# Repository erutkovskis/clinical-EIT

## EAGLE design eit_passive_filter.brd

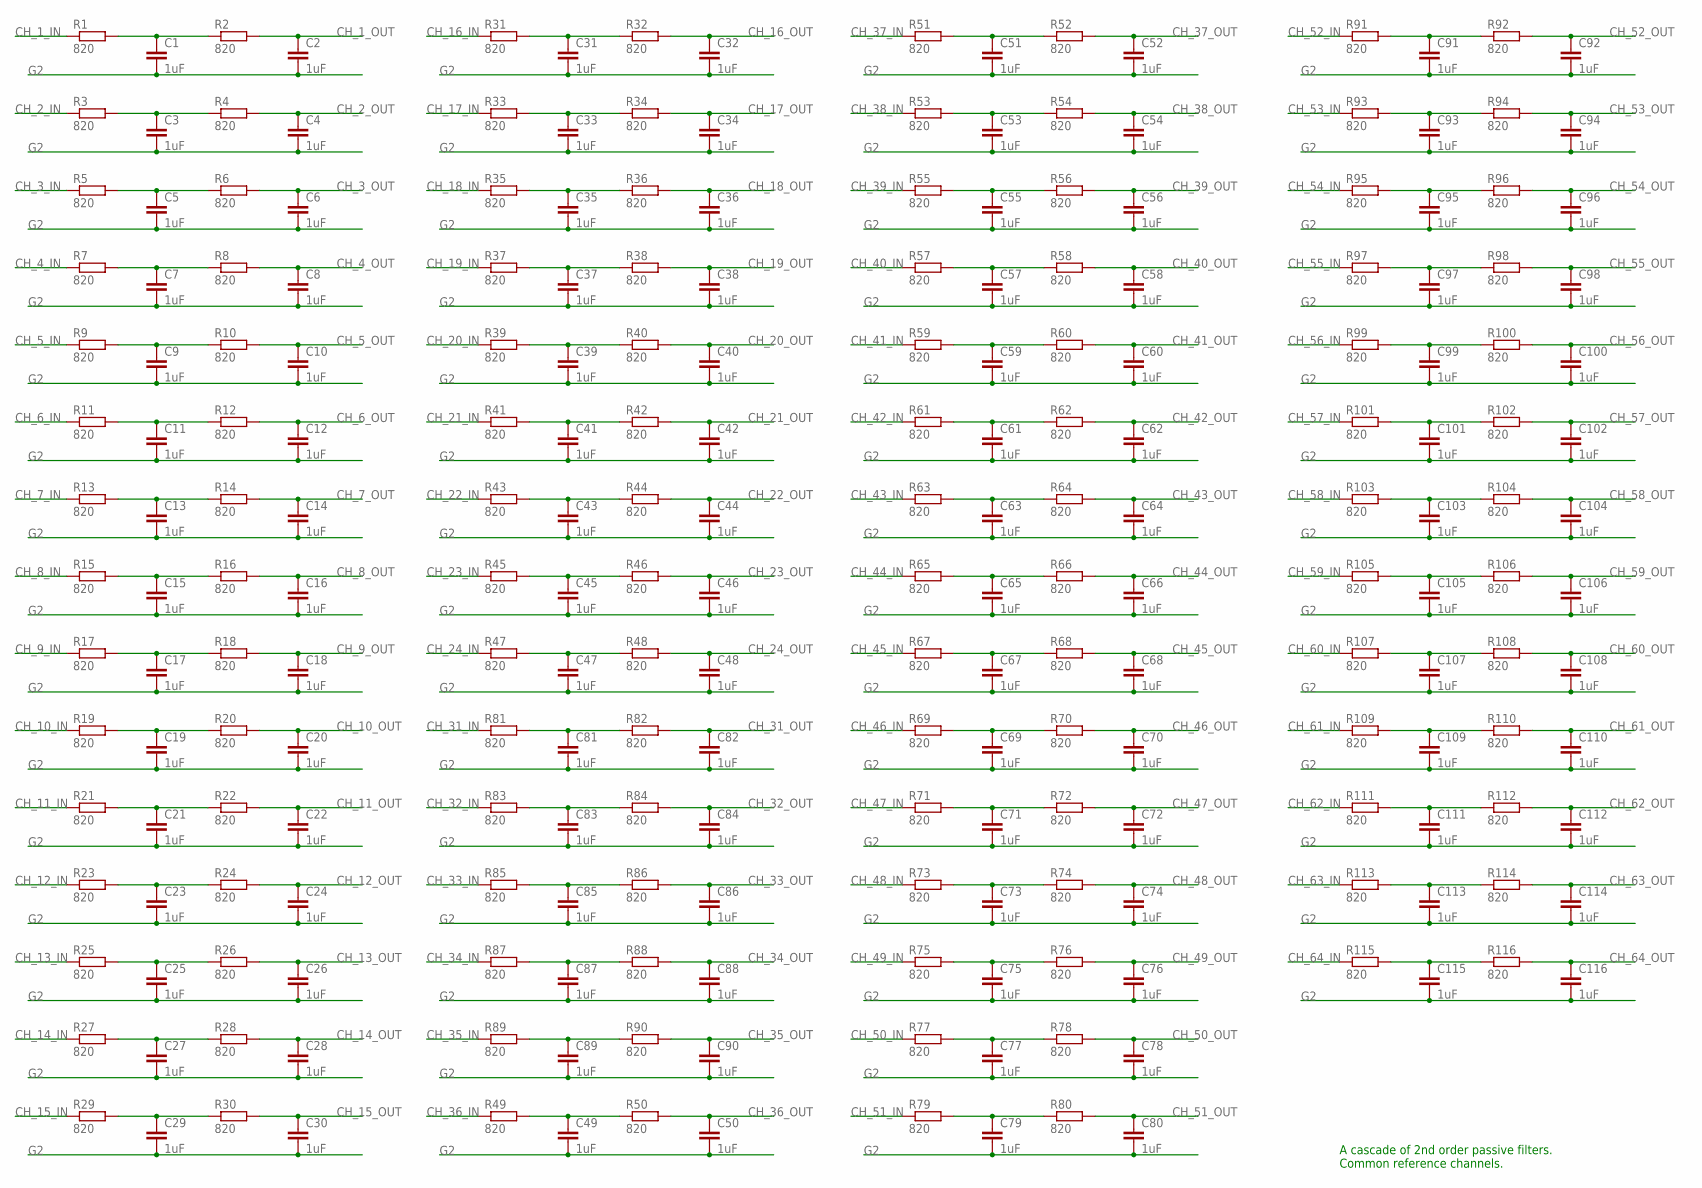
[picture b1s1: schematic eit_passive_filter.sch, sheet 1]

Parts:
C1, C2, C3, C4, C5, C6, C7, C8, C9, C10, C11, C12, C13, C14, C15, C16, C17, C18, C19, C20, C21, C22, C23, C24, C25, C26, C27, C28, C29, C30, C31, C32, C33, C34, C35, C36, C37, C38, C39, C40, C41, C42, C43, C44, C45, C46, C47, C48, C49, C50, C51, C52, C53, C54, C55, C56, C57, C58, C59, C60, C61, C62, C63, C64, C65, C66, C67, C68, C69, C70, C71, C72, C73, C74, C75, C76, C77, C78, C79, C80, C81, C82, C83, C84, C85, C86, C87, C88, C89, C90, C91, C92, C93, C94, C95, C96, C97, C98, C99, C100, C101, C102, C103, C104, C105, C106, C107, C108, C109, C110, C111, C112, C113, C114, C115, C116: 1uF; C0402
R1, R2, R3, R4, R5, R6, R7, R8, R9, R10, R11, R12, R13, R14, R15, R16, R17, R18, R19, R20, R21, R22, R23, R24, R25, R26, R27, R28, R29, R30, R31, R32, R33, R34, R35, R36, R37, R38, R39, R40, R41, R42, R43, R44, R45, R46, R47, R48, R49, R50, R51, R52, R53, R54, R55, R56, R57, R58, R59, R60, R61, R62, R63, R64, R65, R66, R67, R68, R69, R70, R71, R72, R73, R74, R75, R76, R77, R78, R79, R80, R81, R82, R83, R84, R85, R86, R87, R88, R89, R90, R91, R92, R93, R94, R95, R96, R97, R98, R99, R100, R101, R102, R103, R104, R105, R106, R107, R108, R109, R110, R111, R112, R113, R114, R115, R116: 820; R0402

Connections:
CH_1_IN: R1.1; also elsewhere on the board
CH_1_OUT: C2.1, R2.2; also elsewhere on the board
CH_2_IN: R3.1; also elsewhere on the board
CH_2_OUT: C4.1, R4.2; also elsewhere on the board
CH_3_IN: R5.1; also elsewhere on the board
CH_3_OUT: C6.1, R6.2; also elsewhere on the board
CH_4_IN: R7.1; also elsewhere on the board
CH_4_OUT: C8.1, R8.2; also elsewhere on the board
CH_5_IN: R9.1; also elsewhere on the board
CH_5_OUT: C10.1, R10.2; also elsewhere on the board
CH_6_IN: R11.1; also elsewhere on the board
CH_6_OUT: C12.1, R12.2; also elsewhere on the board
CH_7_IN: R13.1; also elsewhere on the board
CH_7_OUT: C14.1, R14.2; also elsewhere on the board
CH_8_IN: R15.1; also elsewhere on the board
CH_8_OUT: C16.1, R16.2; also elsewhere on the board
CH_9_IN: R17.1; also elsewhere on the board
CH_9_OUT: C18.1, R18.2; also elsewhere on the board
CH_10_IN: R19.1; also elsewhere on the board
CH_10_OUT: C20.1, R20.2; also elsewhere on the board
CH_11_IN: R21.1; also elsewhere on the board
CH_11_OUT: C22.1, R22.2; also elsewhere on the board
CH_12_IN: R23.1; also elsewhere on the board
CH_12_OUT: C24.1, R24.2; also elsewhere on the board
CH_13_IN: R25.1; also elsewhere on the board
CH_13_OUT: C26.1, R26.2; also elsewhere on the board
CH_14_IN: R27.1; also elsewhere on the board
CH_14_OUT: C28.1, R28.2; also elsewhere on the board
CH_15_IN: R29.1; also elsewhere on the board
CH_15_OUT: C30.1, R30.2; also elsewhere on the board
CH_16_IN: R31.1; also elsewhere on the board
CH_16_OUT: C32.1, R32.2; also elsewhere on the board
CH_17_IN: R33.1; also elsewhere on the board
CH_17_OUT: C34.1, R34.2; also elsewhere on the board
CH_18_IN: R35.1; also elsewhere on the board
CH_18_OUT: C36.1, R36.2; also elsewhere on the board
CH_19_IN: R37.1; also elsewhere on the board
CH_19_OUT: C38.1, R38.2; also elsewhere on the board
CH_20_IN: R39.1; also elsewhere on the board
CH_20_OUT: C40.1, R40.2; also elsewhere on the board
CH_21_IN: R41.1; also elsewhere on the board
CH_21_OUT: C42.1, R42.2; also elsewhere on the board
CH_22_IN: R43.1; also elsewhere on the board
CH_22_OUT: C44.1, R44.2; also elsewhere on the board
CH_23_IN: R45.1; also elsewhere on the board
CH_23_OUT: C46.1, R46.2; also elsewhere on the board
CH_24_IN: R47.1; also elsewhere on the board
CH_24_OUT: C48.1, R48.2; also elsewhere on the board
CH_31_IN: R81.1; also elsewhere on the board
CH_31_OUT: C82.1, R82.2; also elsewhere on the board
CH_32_IN: R83.1; also elsewhere on the board
CH_32_OUT: C84.1, R84.2; also elsewhere on the board
CH_33_IN: R85.1; also elsewhere on the board
CH_33_OUT: C86.1, R86.2; also elsewhere on the board
CH_34_IN: R87.1; also elsewhere on the board
CH_34_OUT: C88.1, R88.2; also elsewhere on the board
CH_35_IN: R89.1; also elsewhere on the board
CH_35_OUT: C90.1, R90.2; also elsewhere on the board
CH_36_IN: R49.1; also elsewhere on the board
CH_36_OUT: C50.1, R50.2; also elsewhere on the board
CH_37_IN: R51.1; also elsewhere on the board
CH_37_OUT: C52.1, R52.2; also elsewhere on the board
CH_38_IN: R53.1; also elsewhere on the board
CH_38_OUT: C54.1, R54.2; also elsewhere on the board
CH_39_IN: R55.1; also elsewhere on the board
CH_39_OUT: C56.1, R56.2; also elsewhere on the board
CH_40_IN: R57.1; also elsewhere on the board
CH_40_OUT: C58.1, R58.2; also elsewhere on the board
CH_41_IN: R59.1; also elsewhere on the board
CH_41_OUT: C60.1, R60.2; also elsewhere on the board
CH_42_IN: R61.1; also elsewhere on the board
CH_42_OUT: C62.1, R62.2; also elsewhere on the board
CH_43_IN: R63.1; also elsewhere on the board
CH_43_OUT: C64.1, R64.2; also elsewhere on the board
CH_44_IN: R65.1; also elsewhere on the board
CH_44_OUT: C66.1, R66.2; also elsewhere on the board
CH_45_IN: R67.1; also elsewhere on the board
CH_45_OUT: C68.1, R68.2; also elsewhere on the board
CH_46_IN: R69.1; also elsewhere on the board
CH_46_OUT: C70.1, R70.2; also elsewhere on the board
CH_47_IN: R71.1; also elsewhere on the board
CH_47_OUT: C72.1, R72.2; also elsewhere on the board
CH_48_IN: R73.1; also elsewhere on the board
CH_48_OUT: C74.1, R74.2; also elsewhere on the board
CH_49_IN: R75.1; also elsewhere on the board
CH_49_OUT: C76.1, R76.2; also elsewhere on the board
CH_50_IN: R77.1; also elsewhere on the board
CH_50_OUT: C78.1, R78.2; also elsewhere on the board
CH_51_IN: R79.1; also elsewhere on the board
CH_51_OUT: C80.1, R80.2; also elsewhere on the board
CH_52_IN: R91.1; also elsewhere on the board
CH_52_OUT: C92.1, R92.2; also elsewhere on the board
CH_53_IN: R93.1; also elsewhere on the board
CH_53_OUT: C94.1, R94.2; also elsewhere on the board
CH_54_IN: R95.1; also elsewhere on the board
CH_54_OUT: C96.1, R96.2; also elsewhere on the board
CH_55_IN: R97.1; also elsewhere on the board
CH_55_OUT: C98.1, R98.2; also elsewhere on the board
CH_56_IN: R99.1; also elsewhere on the board
CH_56_OUT: C100.1, R100.2; also elsewhere on the board
CH_57_IN: R101.1; also elsewhere on the board
CH_57_OUT: C102.1, R102.2; also elsewhere on the board
CH_58_IN: R103.1; also elsewhere on the board
CH_58_OUT: C104.1, R104.2; also elsewhere on the board
CH_59_IN: R105.1; also elsewhere on the board
CH_59_OUT: C106.1, R106.2; also elsewhere on the board
CH_60_IN: R107.1; also elsewhere on the board
CH_60_OUT: C108.1, R108.2; also elsewhere on the board
CH_61_IN: R109.1; also elsewhere on the board
CH_61_OUT: C110.1, R110.2; also elsewhere on the board
CH_62_IN: R111.1; also elsewhere on the board
CH_62_OUT: C112.1, R112.2; also elsewhere on the board
CH_63_IN: R113.1; also elsewhere on the board
CH_63_OUT: C114.1, R114.2; also elsewhere on the board
CH_64_IN: R115.1; also elsewhere on the board
CH_64_OUT: C116.1, R116.2; also elsewhere on the board
G2: C1.2, C2.2, C3.2, C4.2, C5.2, C6.2, C7.2, C8.2, C9.2, C10.2, C11.2, C12.2, C13.2, C14.2, C15.2, C16.2, C17.2, C18.2, C19.2, C20.2, C21.2, C22.2, C23.2, C24.2, C25.2, C26.2, C27.2, C28.2, C29.2, C30.2, C31.2, C32.2, C33.2, C34.2, C35.2, C36.2, C37.2, C38.2, C39.2, C40.2, C41.2, C42.2, C43.2, C44.2, C45.2, C46.2, C47.2, C48.2, C49.2, C50.2, C51.2, C52.2, C53.2, C54.2, C55.2, C56.2, C57.2, C58.2, C59.2, C60.2, C61.2, C62.2, C63.2, C64.2, C65.2, C66.2, C67.2, C68.2, C69.2, C70.2, C71.2, C72.2, C73.2, C74.2, C75.2, C76.2, C77.2, C78.2, C79.2, C80.2, C81.2, C82.2, C83.2, C84.2, C85.2, C86.2, C87.2, C88.2, C89.2, C90.2, C91.2, C92.2, C93.2, C94.2, C95.2, C96.2, C97.2, C98.2, C99.2, C100.2, C101.2, C102.2, C103.2, C104.2, C105.2, C106.2, C107.2, C108.2, C109.2, C110.2, C111.2, C112.2, C113.2, C114.2, C115.2, C116.2; also elsewhere on the board
unnamed: C1.1, R1.2, R2.1
unnamed: C3.1, R3.2, R4.1
unnamed: C5.1, R5.2, R6.1
unnamed: C7.1, R7.2, R8.1
unnamed: C9.1, R9.2, R10.1
unnamed: C11.1, R11.2, R12.1
unnamed: C13.1, R13.2, R14.1
unnamed: C15.1, R15.2, R16.1
unnamed: C17.1, R17.2, R18.1
unnamed: C19.1, R19.2, R20.1
unnamed: C21.1, R21.2, R22.1
unnamed: C23.1, R23.2, R24.1
unnamed: C25.1, R25.2, R26.1
unnamed: C27.1, R27.2, R28.1
unnamed: C29.1, R29.2, R30.1
unnamed: C31.1, R31.2, R32.1
unnamed: C33.1, R33.2, R34.1
unnamed: C35.1, R35.2, R36.1
unnamed: C37.1, R37.2, R38.1
unnamed: C39.1, R39.2, R40.1
unnamed: C41.1, R41.2, R42.1
unnamed: C43.1, R43.2, R44.1
unnamed: C45.1, R45.2, R46.1
unnamed: C47.1, R47.2, R48.1
unnamed: C49.1, R49.2, R50.1
unnamed: C51.1, R51.2, R52.1
unnamed: C53.1, R53.2, R54.1
unnamed: C55.1, R55.2, R56.1
unnamed: C57.1, R57.2, R58.1
unnamed: C59.1, R59.2, R60.1
unnamed: C61.1, R61.2, R62.1
unnamed: C63.1, R63.2, R64.1
unnamed: C65.1, R65.2, R66.1
unnamed: C67.1, R67.2, R68.1
unnamed: C69.1, R69.2, R70.1
unnamed: C71.1, R71.2, R72.1
unnamed: C73.1, R73.2, R74.1
unnamed: C75.1, R75.2, R76.1
unnamed: C77.1, R77.2, R78.1
unnamed: C79.1, R79.2, R80.1
unnamed: C81.1, R81.2, R82.1
unnamed: C83.1, R83.2, R84.1
unnamed: C85.1, R85.2, R86.1
unnamed: C87.1, R87.2, R88.1
unnamed: C89.1, R89.2, R90.1
unnamed: C91.1, R91.2, R92.1
unnamed: C93.1, R93.2, R94.1
unnamed: C95.1, R95.2, R96.1
unnamed: C97.1, R97.2, R98.1
unnamed: C99.1, R99.2, R100.1
unnamed: C101.1, R101.2, R102.1
unnamed: C103.1, R103.2, R104.1
unnamed: C105.1, R105.2, R106.1
unnamed: C107.1, R107.2, R108.1
unnamed: C109.1, R109.2, R110.1
unnamed: C111.1, R111.2, R112.1
unnamed: C113.1, R113.2, R114.1
unnamed: C115.1, R115.2, R116.1

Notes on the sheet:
A cascade of 2nd order passive filters. Common reference channels.

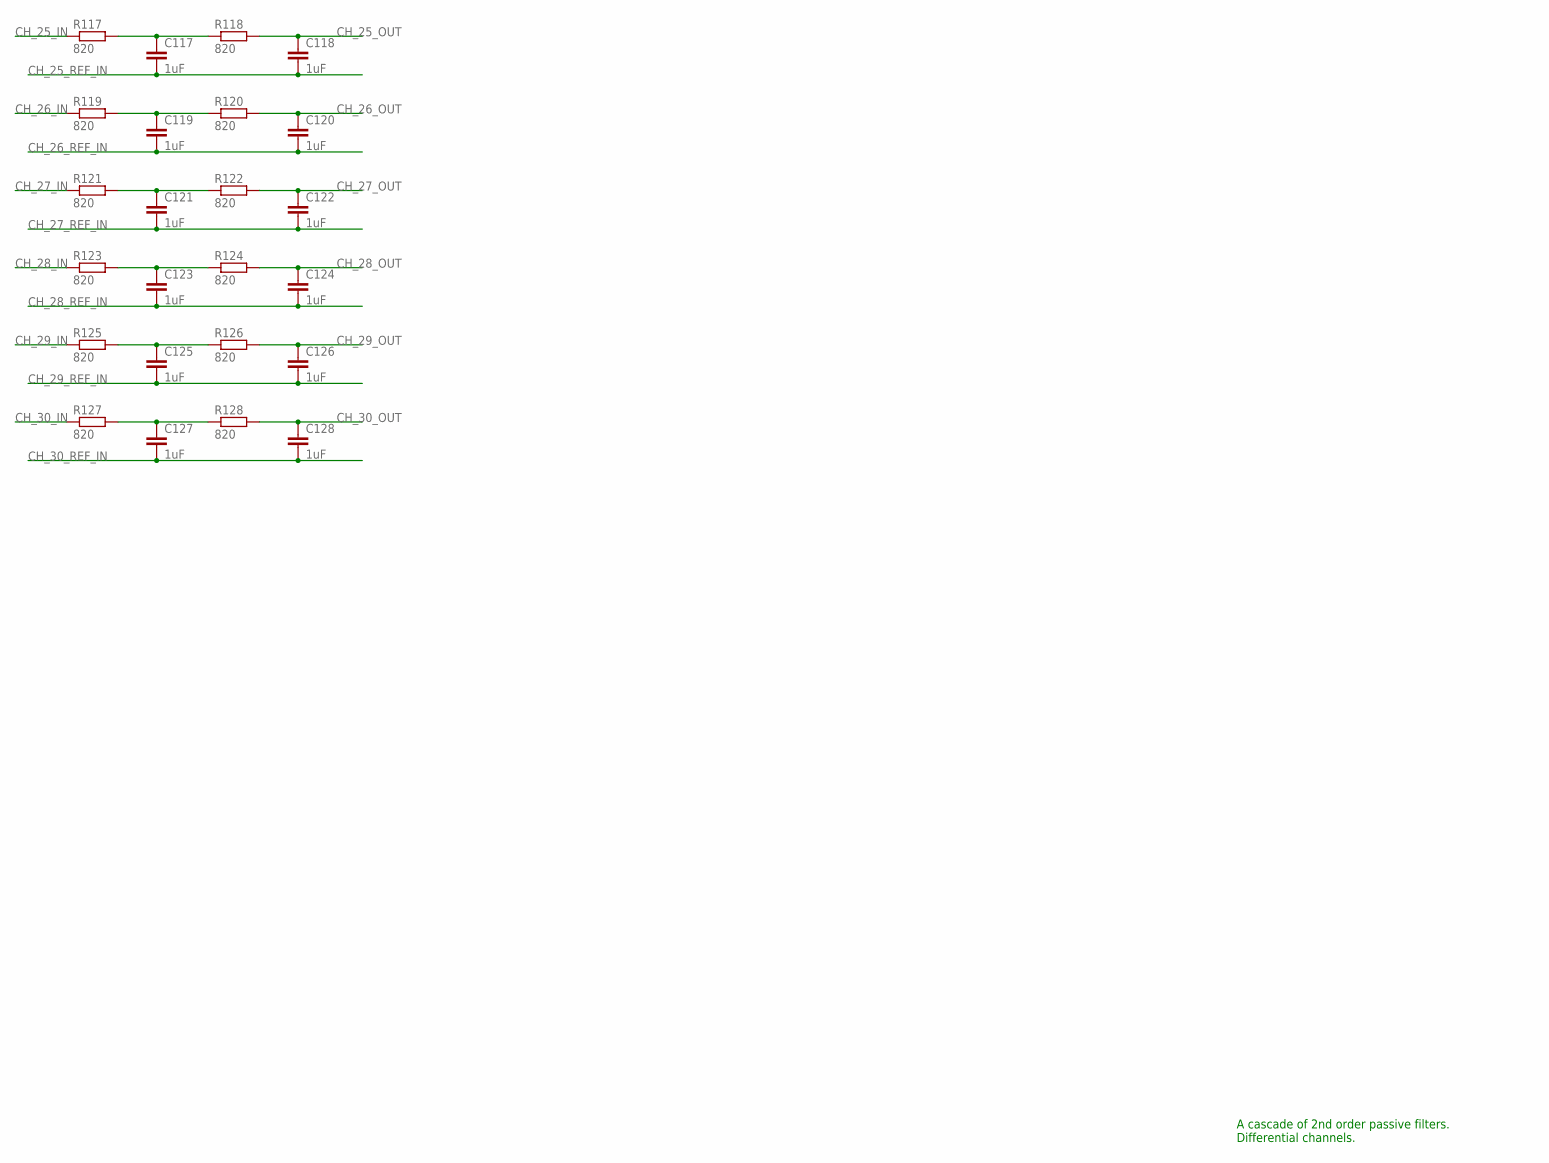
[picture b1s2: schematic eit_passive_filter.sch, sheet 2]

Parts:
C117, C118, C119, C120, C121, C122, C123, C124, C125, C126, C127, C128: 1uF; C0402
R117, R118, R119, R120, R121, R122, R123, R124, R125, R126, R127, R128: 820; R0402

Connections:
CH_25_IN: R117.1; also elsewhere on the board
CH_25_OUT: C118.1, R118.2; also elsewhere on the board
CH_25_REF_IN: C117.2, C118.2; also elsewhere on the board
CH_26_IN: R119.1; also elsewhere on the board
CH_26_OUT: C120.1, R120.2; also elsewhere on the board
CH_26_REF_IN: C119.2, C120.2; also elsewhere on the board
CH_27_IN: R121.1; also elsewhere on the board
CH_27_OUT: C122.1, R122.2; also elsewhere on the board
CH_27_REF_IN: C121.2, C122.2; also elsewhere on the board
CH_28_IN: R123.1; also elsewhere on the board
CH_28_OUT: C124.1, R124.2; also elsewhere on the board
CH_28_REF_IN: C123.2, C124.2; also elsewhere on the board
CH_29_IN: R125.1; also elsewhere on the board
CH_29_OUT: C126.1, R126.2; also elsewhere on the board
CH_29_REF_IN: C125.2, C126.2; also elsewhere on the board
CH_30_IN: R127.1; also elsewhere on the board
CH_30_OUT: C128.1, R128.2; also elsewhere on the board
CH_30_REF_IN: C127.2, C128.2; also elsewhere on the board
unnamed: C117.1, R117.2, R118.1
unnamed: C119.1, R119.2, R120.1
unnamed: C121.1, R121.2, R122.1
unnamed: C123.1, R123.2, R124.1
unnamed: C125.1, R125.2, R126.1
unnamed: C127.1, R127.2, R128.1

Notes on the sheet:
A cascade of 2nd order passive filters. Differential channels.

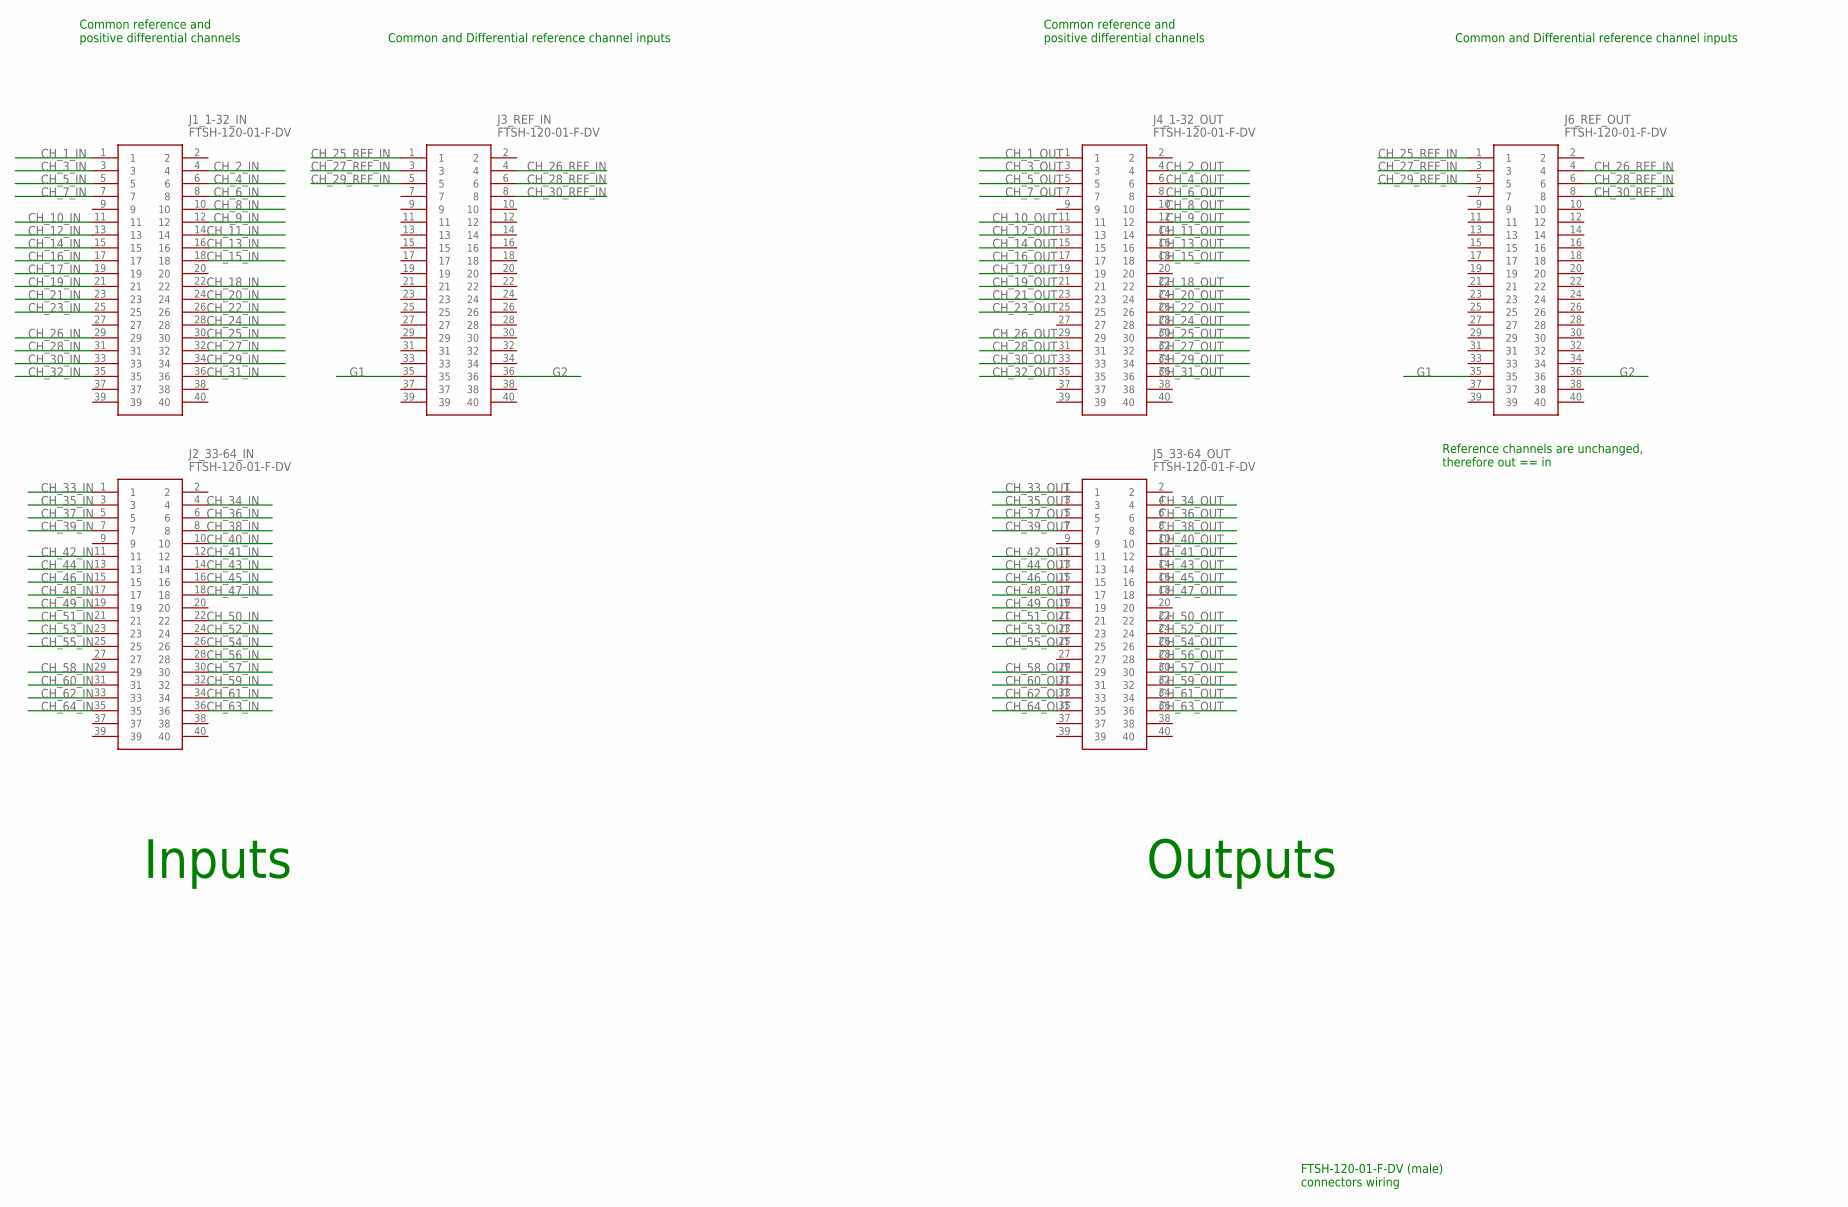
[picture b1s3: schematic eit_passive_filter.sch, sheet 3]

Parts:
J1_1-32_IN, J2_33-64_IN, J3_REF_IN, J4_1-32_OUT, J5_33-64_OUT, J6_REF_OUT: FTSH-120-01-F-DV; FTSH-120-XX-YYY-DV

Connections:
CH_1_IN: J1_1-32_IN.1; also elsewhere on the board
CH_1_OUT: J4_1-32_OUT.1; also elsewhere on the board
CH_2_IN: J1_1-32_IN.4; also elsewhere on the board
CH_2_OUT: J4_1-32_OUT.4; also elsewhere on the board
CH_3_IN: J1_1-32_IN.3; also elsewhere on the board
CH_3_OUT: J4_1-32_OUT.3; also elsewhere on the board
CH_4_IN: J1_1-32_IN.6; also elsewhere on the board
CH_4_OUT: J4_1-32_OUT.6; also elsewhere on the board
CH_5_IN: J1_1-32_IN.5; also elsewhere on the board
CH_5_OUT: J4_1-32_OUT.5; also elsewhere on the board
CH_6_IN: J1_1-32_IN.8; also elsewhere on the board
CH_6_OUT: J4_1-32_OUT.8; also elsewhere on the board
CH_7_IN: J1_1-32_IN.7; also elsewhere on the board
CH_7_OUT: J4_1-32_OUT.7; also elsewhere on the board
CH_8_IN: J1_1-32_IN.10; also elsewhere on the board
CH_8_OUT: J4_1-32_OUT.10; also elsewhere on the board
CH_9_IN: J1_1-32_IN.12; also elsewhere on the board
CH_9_OUT: J4_1-32_OUT.12; also elsewhere on the board
CH_10_IN: J1_1-32_IN.11; also elsewhere on the board
CH_10_OUT: J4_1-32_OUT.11; also elsewhere on the board
CH_11_IN: J1_1-32_IN.14; also elsewhere on the board
CH_11_OUT: J4_1-32_OUT.14; also elsewhere on the board
CH_12_IN: J1_1-32_IN.13; also elsewhere on the board
CH_12_OUT: J4_1-32_OUT.13; also elsewhere on the board
CH_13_IN: J1_1-32_IN.16; also elsewhere on the board
CH_13_OUT: J4_1-32_OUT.16; also elsewhere on the board
CH_14_IN: J1_1-32_IN.15; also elsewhere on the board
CH_14_OUT: J4_1-32_OUT.15; also elsewhere on the board
CH_15_IN: J1_1-32_IN.18; also elsewhere on the board
CH_15_OUT: J4_1-32_OUT.18; also elsewhere on the board
CH_16_IN: J1_1-32_IN.17; also elsewhere on the board
CH_16_OUT: J4_1-32_OUT.17; also elsewhere on the board
CH_17_IN: J1_1-32_IN.19; also elsewhere on the board
CH_17_OUT: J4_1-32_OUT.19; also elsewhere on the board
CH_18_IN: J1_1-32_IN.22; also elsewhere on the board
CH_18_OUT: J4_1-32_OUT.22; also elsewhere on the board
CH_19_IN: J1_1-32_IN.21; also elsewhere on the board
CH_19_OUT: J4_1-32_OUT.21; also elsewhere on the board
CH_20_IN: J1_1-32_IN.24; also elsewhere on the board
CH_20_OUT: J4_1-32_OUT.24; also elsewhere on the board
CH_21_IN: J1_1-32_IN.23; also elsewhere on the board
CH_21_OUT: J4_1-32_OUT.23; also elsewhere on the board
CH_22_IN: J1_1-32_IN.26; also elsewhere on the board
CH_22_OUT: J4_1-32_OUT.26; also elsewhere on the board
CH_23_IN: J1_1-32_IN.25; also elsewhere on the board
CH_23_OUT: J4_1-32_OUT.25; also elsewhere on the board
CH_24_IN: J1_1-32_IN.28; also elsewhere on the board
CH_24_OUT: J4_1-32_OUT.28; also elsewhere on the board
CH_25_IN: J1_1-32_IN.30; also elsewhere on the board
CH_25_OUT: J4_1-32_OUT.30; also elsewhere on the board
CH_25_REF_IN: J3_REF_IN.1, J6_REF_OUT.1; also elsewhere on the board
CH_26_IN: J1_1-32_IN.29; also elsewhere on the board
CH_26_OUT: J4_1-32_OUT.29; also elsewhere on the board
CH_26_REF_IN: J3_REF_IN.4, J6_REF_OUT.4; also elsewhere on the board
CH_27_IN: J1_1-32_IN.32; also elsewhere on the board
CH_27_OUT: J4_1-32_OUT.32; also elsewhere on the board
CH_27_REF_IN: J3_REF_IN.3, J6_REF_OUT.3; also elsewhere on the board
CH_28_IN: J1_1-32_IN.31; also elsewhere on the board
CH_28_OUT: J4_1-32_OUT.31; also elsewhere on the board
CH_28_REF_IN: J3_REF_IN.6, J6_REF_OUT.6; also elsewhere on the board
CH_29_IN: J1_1-32_IN.34; also elsewhere on the board
CH_29_OUT: J4_1-32_OUT.34; also elsewhere on the board
CH_29_REF_IN: J3_REF_IN.5, J6_REF_OUT.5; also elsewhere on the board
CH_30_IN: J1_1-32_IN.33; also elsewhere on the board
CH_30_OUT: J4_1-32_OUT.33; also elsewhere on the board
CH_30_REF_IN: J3_REF_IN.8, J6_REF_OUT.8; also elsewhere on the board
CH_31_IN: J1_1-32_IN.36; also elsewhere on the board
CH_31_OUT: J4_1-32_OUT.36; also elsewhere on the board
CH_32_IN: J1_1-32_IN.35; also elsewhere on the board
CH_32_OUT: J4_1-32_OUT.35; also elsewhere on the board
CH_33_IN: J2_33-64_IN.1; also elsewhere on the board
CH_33_OUT: J5_33-64_OUT.1; also elsewhere on the board
CH_34_IN: J2_33-64_IN.4; also elsewhere on the board
CH_34_OUT: J5_33-64_OUT.4; also elsewhere on the board
CH_35_IN: J2_33-64_IN.3; also elsewhere on the board
CH_35_OUT: J5_33-64_OUT.3; also elsewhere on the board
CH_36_IN: J2_33-64_IN.6; also elsewhere on the board
CH_36_OUT: J5_33-64_OUT.6; also elsewhere on the board
CH_37_IN: J2_33-64_IN.5; also elsewhere on the board
CH_37_OUT: J5_33-64_OUT.5; also elsewhere on the board
CH_38_IN: J2_33-64_IN.8; also elsewhere on the board
CH_38_OUT: J5_33-64_OUT.8; also elsewhere on the board
CH_39_IN: J2_33-64_IN.7; also elsewhere on the board
CH_39_OUT: J5_33-64_OUT.7; also elsewhere on the board
CH_40_IN: J2_33-64_IN.10; also elsewhere on the board
CH_40_OUT: J5_33-64_OUT.10; also elsewhere on the board
CH_41_IN: J2_33-64_IN.12; also elsewhere on the board
CH_41_OUT: J5_33-64_OUT.12; also elsewhere on the board
CH_42_IN: J2_33-64_IN.11; also elsewhere on the board
CH_42_OUT: J5_33-64_OUT.11; also elsewhere on the board
CH_43_IN: J2_33-64_IN.14; also elsewhere on the board
CH_43_OUT: J5_33-64_OUT.14; also elsewhere on the board
CH_44_IN: J2_33-64_IN.13; also elsewhere on the board
CH_44_OUT: J5_33-64_OUT.13; also elsewhere on the board
CH_45_IN: J2_33-64_IN.16; also elsewhere on the board
CH_45_OUT: J5_33-64_OUT.16; also elsewhere on the board
CH_46_IN: J2_33-64_IN.15; also elsewhere on the board
CH_46_OUT: J5_33-64_OUT.15; also elsewhere on the board
CH_47_IN: J2_33-64_IN.18; also elsewhere on the board
CH_47_OUT: J5_33-64_OUT.18; also elsewhere on the board
CH_48_IN: J2_33-64_IN.17; also elsewhere on the board
CH_48_OUT: J5_33-64_OUT.17; also elsewhere on the board
CH_49_IN: J2_33-64_IN.19; also elsewhere on the board
CH_49_OUT: J5_33-64_OUT.19; also elsewhere on the board
CH_50_IN: J2_33-64_IN.22; also elsewhere on the board
CH_50_OUT: J5_33-64_OUT.22; also elsewhere on the board
CH_51_IN: J2_33-64_IN.21; also elsewhere on the board
CH_51_OUT: J5_33-64_OUT.21; also elsewhere on the board
CH_52_IN: J2_33-64_IN.24; also elsewhere on the board
CH_52_OUT: J5_33-64_OUT.24; also elsewhere on the board
CH_53_IN: J2_33-64_IN.23; also elsewhere on the board
CH_53_OUT: J5_33-64_OUT.23; also elsewhere on the board
CH_54_IN: J2_33-64_IN.26; also elsewhere on the board
CH_54_OUT: J5_33-64_OUT.26; also elsewhere on the board
CH_55_IN: J2_33-64_IN.25; also elsewhere on the board
CH_55_OUT: J5_33-64_OUT.25; also elsewhere on the board
CH_56_IN: J2_33-64_IN.28; also elsewhere on the board
CH_56_OUT: J5_33-64_OUT.28; also elsewhere on the board
CH_57_IN: J2_33-64_IN.30; also elsewhere on the board
CH_57_OUT: J5_33-64_OUT.30; also elsewhere on the board
CH_58_IN: J2_33-64_IN.29; also elsewhere on the board
CH_58_OUT: J5_33-64_OUT.29; also elsewhere on the board
CH_59_IN: J2_33-64_IN.32; also elsewhere on the board
CH_59_OUT: J5_33-64_OUT.32; also elsewhere on the board
CH_60_IN: J2_33-64_IN.31; also elsewhere on the board
CH_60_OUT: J5_33-64_OUT.31; also elsewhere on the board
CH_61_IN: J2_33-64_IN.34; also elsewhere on the board
CH_61_OUT: J5_33-64_OUT.34; also elsewhere on the board
CH_62_IN: J2_33-64_IN.33; also elsewhere on the board
CH_62_OUT: J5_33-64_OUT.33; also elsewhere on the board
CH_63_IN: J2_33-64_IN.36; also elsewhere on the board
CH_63_OUT: J5_33-64_OUT.36; also elsewhere on the board
CH_64_IN: J2_33-64_IN.35; also elsewhere on the board
CH_64_OUT: J5_33-64_OUT.35; also elsewhere on the board
G1: J3_REF_IN.35, J6_REF_OUT.35
G2: J3_REF_IN.36, J6_REF_OUT.36; also elsewhere on the board

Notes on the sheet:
FTSH-120-01-F-DV (male) connectors wiring
Common reference and positive differential channels
Common and Differential reference channel inputs
Inputs
Outputs
Reference channels are unchanged, therefore out == in

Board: 2 copper layers, 262 parts (3 on the bottom side), 200 nets, no tracks yet.

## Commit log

2024-02-19 Checkpoint 1. Finished passive filter schematic topology. Begin component placement and routing.
